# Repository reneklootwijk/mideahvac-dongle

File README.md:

# Midea HVAC WiFi Dongle

This repository contains the hardware design of a WiFi dongle for Midea-like airconditioners and humidifiers.
Midea provides a WiFi dongle (SK102/SK103), either as optional feature or built-in, to control the appliances via a mobile application. This dongle uses and is dependent on the Midea cloud which does not expose a publically available API. The protocol used by the dongle has been reverse engineered, but newer version still require the cloud to obtain an encryption key or require an addition server simulating the Midea cloud. This means integration in an existing home automation system is not straight forward.

Besides the protocol the dongle uses to commumicate with the mobile app and the cloud, also the protocol that is used between the dongle and the appliances has been reverse engineered (at least the most important parts). This means the original dongle can be replaced by a custom dongle making it independent on any cloud.

Besides Midea itself other vendors of these type of appliances are also using the Midea cloud and dongle to support control via a mobile app. Examples of these vendors are:

* Qlima
* Artel
* Carrier
* Toshiba
* Idema
* Dimstal/Simando

This design of a custom dongle can be used to replace the orignal dongle with a type A USB connector. The version with with a JST-XH connector needs a slight modification.

## Technical design

The design of the dongle is based on an ESP-12 which provides the WiFi interface and microcontroller to communicate with the appliance. Because the interface of the appliance is a 5V TTL serial port (UART) and the ESP-12 uses 3.3V and is not 5V tolerant, we need level shifters for the communication and a power regulator in order to power the dongle from the appliance.

The design has been made in KiCad and all files can be found in the KiCad directory.

<p align="center">
  <br/>
  <em>The KiCad PCB design</em>
</p>

Note: The resulting PCB including the ESP-12 turned out to be 1 mm to long to fit into the location of the original dongle (in my Artel airconditioner). It was easy to locate it somewhere else, but pay attention whether the PCB would fit in your appliance. The dimensions of the dongle are: 55mmx20mm (l*w) without casing.

## Ordering and manufacturing

The PCB can be ordered by the manufacturer of your choosing. I had it manufactured and partly assembled by [JLCPCB](https://jlcpcb.com/). The files required to order the PCB including the SMT assembly of all components except the ESP-12 and USB connector can be found in the JLCPCB directory.

<p align="center">
  <br/>
  <em>The assembled PCB</em>
</p>

The JLCPCB directory contains the following files:

* Gerber-Midea WiFi Dongle v1.zip, this zip contains all gerber files and the drill file.
* BOM-Midea WiFi Dongle.csv, this is the Bill Of Material file.
* CPL-Midea WiFi Dongle.csv, this is the Pick and Place file

Note: The ESP-12 and USB connector are not part of the BOM and need to be ordered somewhere else, JLCPCB could not deliver them. This also means you have to solder them yourself.

## Case

I also designed a case that can printed on a 3d printer. The .STL file is part of this repository.

<p align="center">
  <br/>
  <em>The 3D printed case</em>
</p>

## Firmware

At this moment there are several options:
* Sören Beye created firmware to integrate dehumidifiers with Home Assistant: https://github.com/Hypfer/esp8266-midea-dehumidifier.
* Sergey V. Dudanov created an extension for ESPHome integrating aircondititioners with Home Assistant: https://github.com/dudanov/esphome.
* I created a node.js module to integrate airconditioners with anything you like, but you need to program: https://github.com/reneklootwijk/node-mideahvac. The firmware required on the dongle is esplink, a serial bridge: https://github.com/jeelabs/esp-link.
* To reverse engineer the protocol the original dongle is using to communicate with your appliance, you can use this custom dongle to capture this communication. See https://github.com/reneklootwijk/midea-uartsniffer.

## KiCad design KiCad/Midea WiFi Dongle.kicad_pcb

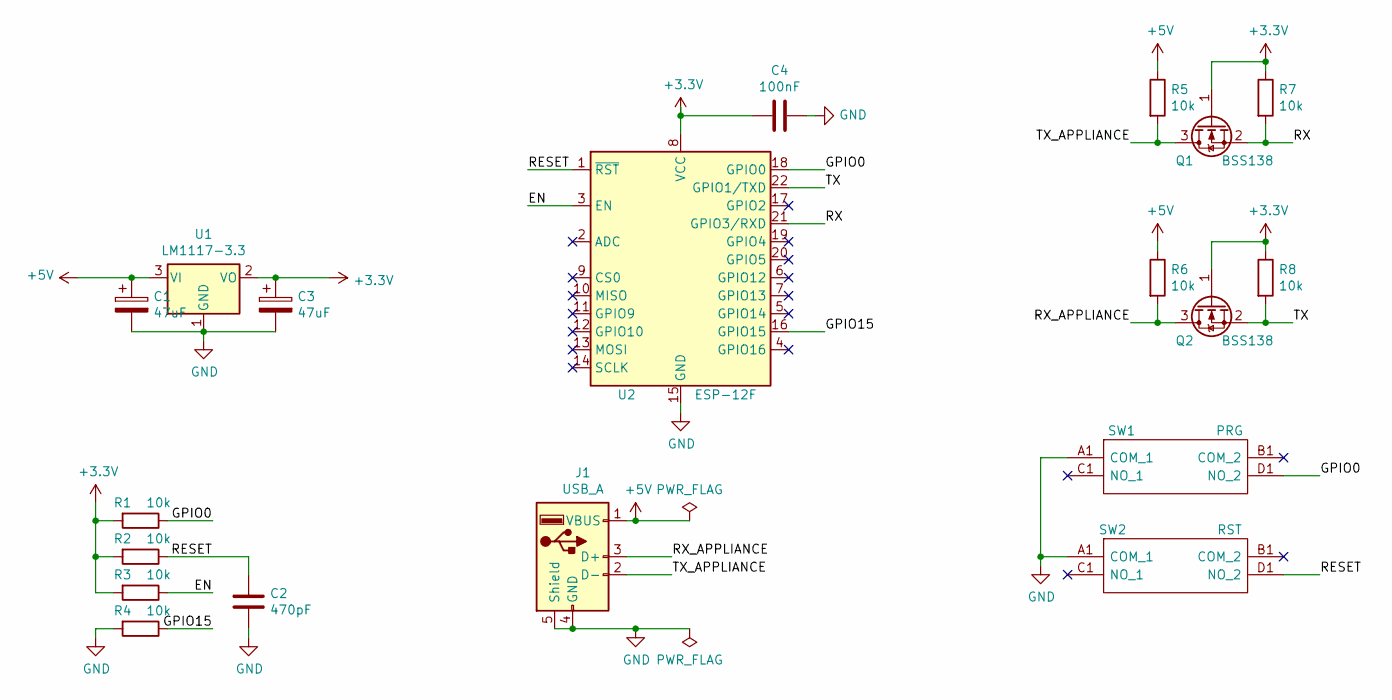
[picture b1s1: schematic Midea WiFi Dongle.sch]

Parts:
C1, C3: 47uF; CP_EIA-3216-10_Kemet-I; LCSC C185773
C2: 470pF; C_0402_1005Metric
C4: 100nF; C_0402_1005Metric
J1: USB_A; USB_A_CNCTech_1001-011-01101_Horizontal
Q1, Q2: BSS138; SOT-23; LCSC C426569
R1, R2, R3, R4, R5, R6, R7, R8: 10k; R_0402_1005Metric; LCSC C25744
SW1: PRG; TS1187AXXX; Manufacturer_Part_Number TS-1187A-C-C-B; LCSC C318889
SW2: RST; TS1187AXXX; Manufacturer_Part_Number TS-1187A-C-C-B; LCSC C318889
U1: LM1117-3.3; SOT-223; LCSC C126027
U2: ESP-12F; ESP-12E

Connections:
+3V3: C3.1, C4.2, Q1.1 (G), Q2.1 (G), R1.2, R2.2, R3.2, R7.1, R8.1, U1.2 (VO), U2.8 (VCC)
+5V: C1.1, J1.1 (VBUS), R5.1, R6.1, U1.3 (VI)
/EN: R3.1, U2.3 (EN)
/GPIO0: R1.1, SW1.D1 (NO_2), U2.18 (GPIO0)
/GPIO15: R4.1, U2.16 (GPIO15)
/RESET: C2.1, R2.1, SW2.D1 (NO_2), U2.1 (~RST)
/RX: Q1.2 (S), R7.2, U2.21 (GPIO3/RXD)
/RX_APPLIANCE: J1.3 (D+), Q2.3 (D), R6.2
/TX: Q2.2 (S), R8.2, U2.22 (GPIO1/TXD)
/TX_APPLIANCE: J1.2 (D-), Q1.3 (D), R5.2
GND: C1.2, C2.2, C3.2, C4.1, J1.4 (GND), J1.5 (Shield), R4.2, SW1.A1 (COM_1), SW2.A1 (COM_1), U1.1 (GND), U2.15 (GND)

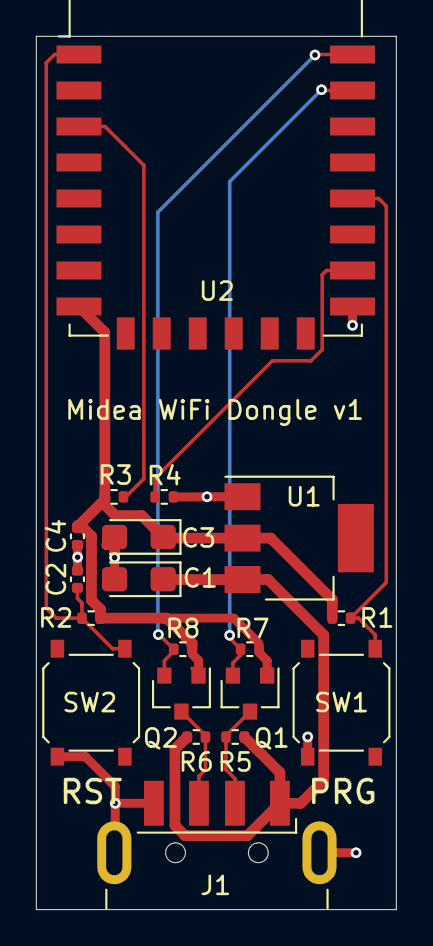
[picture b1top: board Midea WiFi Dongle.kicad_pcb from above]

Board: 4 copper layers, 20.0 x 48.5 mm, 19 parts (0 on the bottom side), 11 nets.

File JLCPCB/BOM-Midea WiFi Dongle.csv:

Comment,Designator, Footprint, LCSC Part #
PRG,SW1,SMD-SW-4_5.1x5.1x1.7,C318889
RST,SW2,SMD-SW-4_5.1x5.1x1.7,C318889
BSS138,Q1,SOT-23,C426569
BSS138,Q2,SOT-23,C426569
100nF,C4,0402,C1525
10k,R5,0402,C25744
10k,R7,0402,C25744
10k,R6,0402,C25744
10k,R8,0402,C25744
LM1117-3.3,U1,SOT-223,C126027
47uF,C3,CASE-A_3216,C185773
47uF,C1,CASE-A_3216,C185773
10k,R1,0402,C25744
10k,R2,0402,C25744
10k,R3,0402,C25744
10k,R4,0402,C25744
470uF,C2,0402,C1537

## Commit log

2020-11-10 Corrected typos and added firmware section
2020-11-10 Corrected typos
2020-11-10 Fixed CPL file
2022-03-29 Update README.md
    Added Dimstal/Simando to the example vendor list. To clarify and save the info its also a midea AC. My monoblock model (SMND-PAC-12) has no USB-Plug, but the 4 pin Header on the Control/Display-PCB i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

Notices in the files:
KiCad/Midea WiFi Dongle.kicad_pcb:
Copyright (C) 2020
